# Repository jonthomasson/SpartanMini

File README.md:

# SpartanMini
A flexible, simple, yet powerful FPGA development board.

As is the case with many things, the Spartan Mini was born out of a need I had when developing an FPGA project. I looked around at the development boards in the market, but I didn't see anything that met all of my requirements, so I decided to design one myself. There were many requirements for this board, which I will go into more detail about in the details section below, but my general requirements were as follows. I wanted a board I could hand solder fairly easily. This meant no bga. I wanted a board that was easy to program, containing both a JTAG port as well as USB. I wanted a board I could power with a wall wart and a barrel jack. The power needed to be switched. There needed to be plenty of GPIO, brought out to connectors that were preferably of a standardized format. I wanted some onboard RAM, preferrably SRAM or PSRAM for ease of use. Other than that I just wanted access to the bare metal of the FPGA, without a lot of fluff.

Continuing from the requirements stated in the description, here is a more in depth look at those requirements and how the Spartan Mini meets them:

1. A board that could be hand soldered fairly easily.

It seems like 90% or more of the FPGA's out there are in a BGA package. This made things difficult when considering this spec. I finally settled on the Spartan 6 FPGA because it came in a 144 pin TQFP package. The Spartan 6 is a well known and well supported FPGA among hackers and makers, making it a perfect candidate for the job.

2. A board that could be programmed easily with either JTAG or USB.

For the USB portion of this requirement, I decide to use the FT2232H chip by FTDI. This chip gave me both a USB to JTAG channel, as well as a USB to UART bridge that I could use later on to facilitate transferring data to the FPGA over the USB connection. I also wanted to include a full size 14 pin JTAG connector on board, to facilitate the use of a Xilinx Platform Cable USB programmer. This took a little more board space, but provides an easier interface to connect to the Xilinx programmer.

3. A board that could be powered with a wall wart and barrel jack.

This requirement was fairly simple to implement. The voltage requirements for the board fall between 3.7-6 volts dc. In addition to the barrel jack, the board provides jumpers to optionally be powered over USB, or a JST-PH connector and 3.7 volt lithium battery, as well as a voltage input pin.

4. The power needed to have a hard on/off switch.

Again, this requirement was not hard to implement. I just needed to select an adequate switch, capable of handling the current demands of the board.

5. No IO pin of the FPGA should be wasted. All pins should be brought out to standardized connectors on the edges of the board.

Many FPGA boards today seem like they waste a lot of IO on providing connectors on board that likely aren't needed by every project such as SD cards, VGA, HDMI, etc. Instead of using up the IO on peripherals that may be unneeded I opted to instead route all GPIO lines out to PMOD connectors. These connectors seem to be picking up in popularity and there are already tons of sensors/peripherals to choose from in the marketplace that can be plugged into the board if/when they're needed. In addition to the GPIO, I also wired GPIO pins to 8 user programmable LED's, 2 tactile buttons, and 1 slide switch. The addition of the 8 LED's aids greatly in debugging, but it also allows for precisely one byte of data to be represented in binary.

6. Access to onboard SRAM or PSRAM

This requirement is simply for the ease of use of SRAM over DRAM. The downside to SRAM is of course the price, which is why I settled on PSRAM instead. Essentially PSRAM provides an interface to the outside world that looks like SRAM, while internally it is made up of DRAM. As such, it is much cheaper than SRAM, but way less work to interface with than DRAM. This particular board provides 8Mb of PSRAM, which is adequate for my needs.

![enter image description here](https://lh3.googleusercontent.com/Ym8JBT1FlSJsortWRAH4dx5KHW2HkV1B4FOYHD6TUoF2Va7fMqjjbZRKk-YTAfOauaZ6iTyjpKmPpW8K9U_Lzy1sPvceVg2OTIK4zidJ0OYhVarUZ6AJo-_n0Bh1tX8kFqed3uyobCEtJzAthKT_NUfyR5vuuTG_k4TjL7J-cD8Y5W50PloVUXzOydISsuWan971t84IHQZvExRTL13VKr9Dzf7VFZQ4-1O7Eb2D59EVHCMWfp65vcO2BCi3f3q-bV_YtxEnLM_6e8DsP4a7GdczFiddMFkXQBkkdZaEMM2iFYc0Uvn_fpE_hW8l_2niM3Bjweu2Sg1JI46zMwf1BJlQvk6hKFwMn6nt-VLBW11oDaMBjqX9CXKMFm71dwxRTxzdKROl2nzPsxBll-ldlJ9pS-G4F2r8SEyl_1cLp4FI9L6Toqehjpdptvo6k-bQtzZX9d7uxOGFWja2dMNWYFRKiI2IBQzqyreGzzcMScAPFWFUQucwtIUtVOjU9eformU7DzSAqNybfNj_1Cf66kgaPlsM0UQ6a2LvAtUDOFYDCX_l58AIW41YAItvtlo8zSZ7KETyjbF2bbkrhY29mfstlfJ0lxFEip1irmiC=w1223-h688-no)

Here's a pic of the finished proto shield:
![enter image description here](https://lh3.googleusercontent.com/XVl9vBILrFzYoo-aqGuPinKMaAg1SiMGnw2o0brUdcbjzrX_OM7FDiEOOaxkABmsGx_YnNGTo_vhjEov2aorHuK09fe5Of0MSD2nyAMjhmHx2-vPp61wXmYYEb9uJpriS7c-KQS3IXlFl3N068_lc_-l7lU_sf3SuPzvnHECnoO0J4L6pnPQVym1PMrDh47Fw-OdFCAAsPRn38aGkLim3vHlUNbdCeJ7o2DY7dQxQNxw3rlYhkYHu8ck_lHzUk-93gGGT9lEoZzGOoJ5PW-e5-kHvbxesEgOWf7VaKeEmJR0SyLdO2nTZNo8BzTyuRD0KrKwcO2678YBeTiLqef4WfJXKnJdRhSgQjhQ-s72llQxLT6zsE_KIJDUy6Yd8EM9Fzlg9KmEdMNf-uqJ4Ht_2Hn0ylL2g0QgoXBpAplv5dJR7Py4TpnUCzPOWrd63cMVwbfEfk8FLc2Xi8dEvnVO9D8D-NkFfG4Thc_I4GchgRej_VKDMysdUIFXAmFLjOvsaycX8eAK-RTY47NzNEG65PhANNQOsBYcIzGDWJXmgfrrhz2uPa8Q47qfnD9Brrmjvd-rsr0FU_VZmEmJzgSOTgQjifBuex9lx5Dea8zO=w1688-h949-no)

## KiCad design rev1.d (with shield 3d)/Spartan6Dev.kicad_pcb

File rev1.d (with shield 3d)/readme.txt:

--Main change from 1.c: I added right angle switches to provide access for eventual daughter boards. I also put sw2 on the board edge to provide additional access if a daughter board was connected. Also added a VIN/GND pin for external power to be fed in via daughter board, etc.

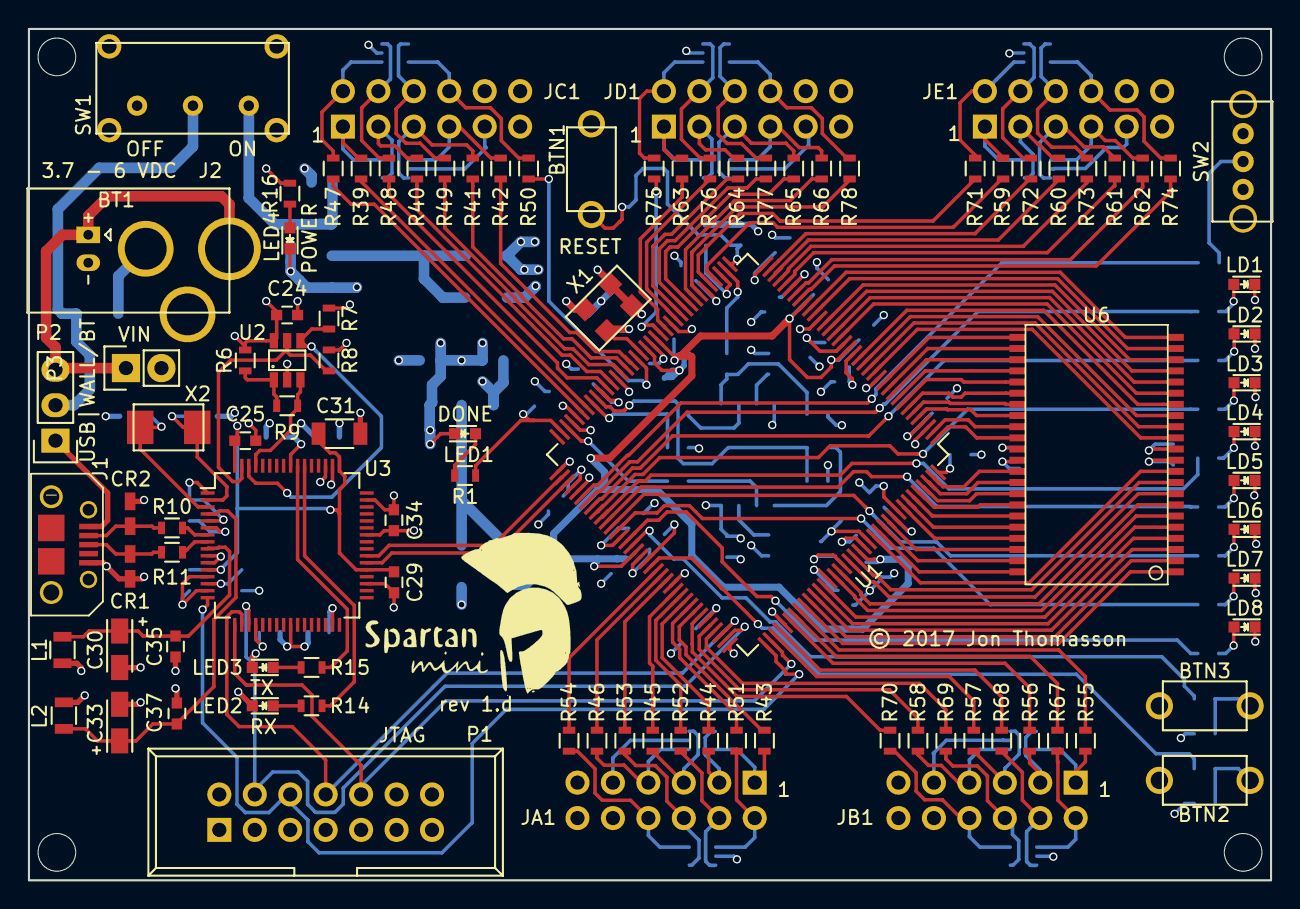
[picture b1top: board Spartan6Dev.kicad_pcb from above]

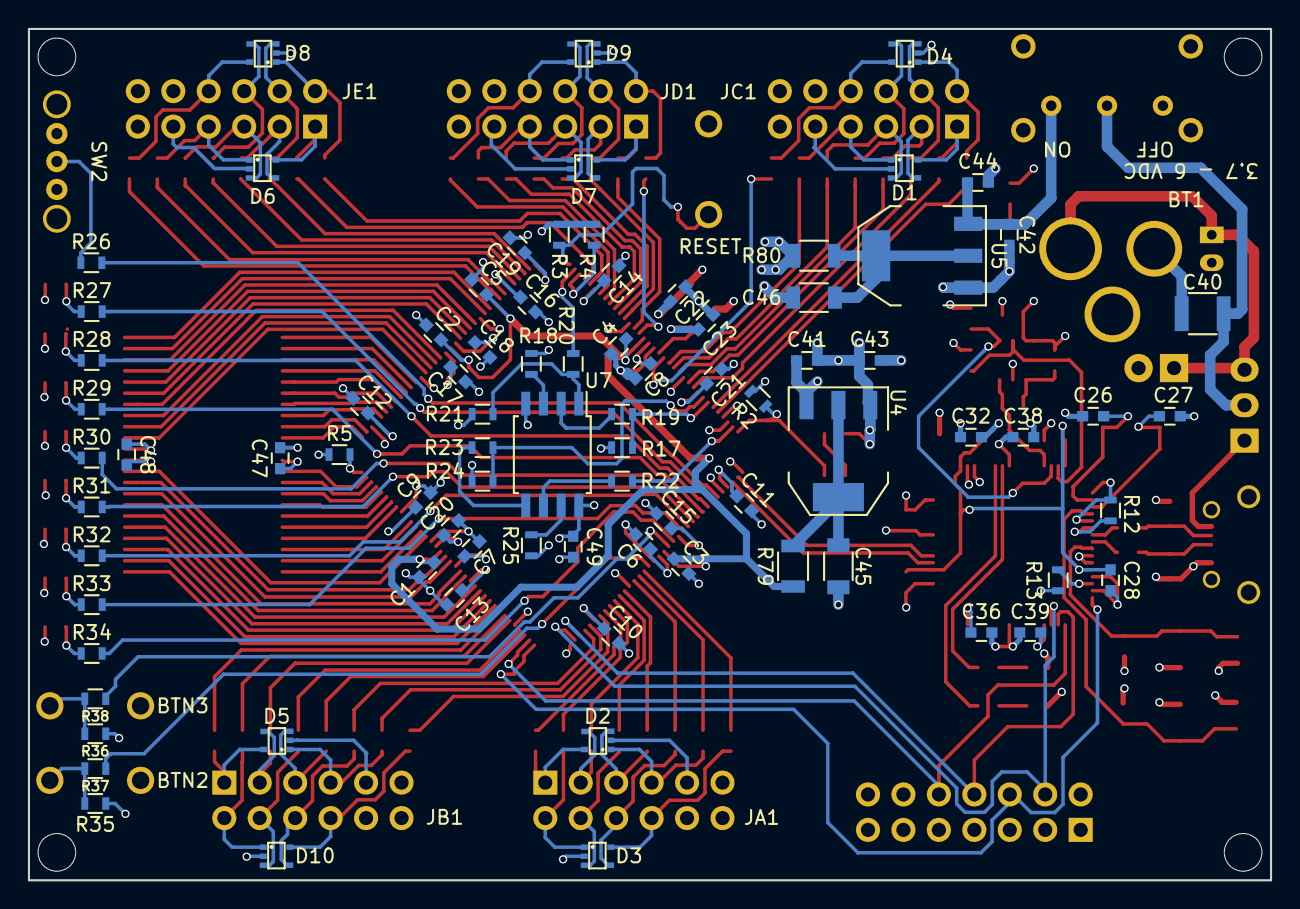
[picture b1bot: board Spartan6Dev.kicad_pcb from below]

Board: 4 copper layers, 89.0 x 61.0 mm, 180 parts (83 on the bottom side), 193 nets.

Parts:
BT1: JST-PH 3.7V BAT; JST_PH_S2B-PH-K_02x2.00mm
BTN1: BTN_RESET; SWITCH_1825966_1
BTN2, BTN3: BTN_PUSH; SWITCH_1825966_1
C1, C2, C3, C4, C5, C6, C7, C8, C9, C10, C11, C12, C13, C14, C15, C16, C17, C18, C19, C20, C21, C24, C25, C28, C29, C32, C34, C35, C36, C37, C38, C39, C41, C42, C47, C48, C49: .1uF; C_0603
C22: .01uF; C_0603
C23, C26, C27: 18pF; C_0603
C30, C33: 4.7uF; TantalC_SizeA_EIA-3216_Reflow
C31: 3.3uF; C_1206
C40: 47uF; C_1210
C43, C44: 1uF; C_0603
C45, C46: 10uF; C_1206
CR1, CR2: D_TVS; D_TVS_PGB1010603
D1, D2, D3, D4, D5, D6, D7, D8, D9, D10: NSQA6V8AW5T2; SOT323_5_NSQA6V8AW5T2
J1: USB MICRO; MICRO_USB_10118194
J2: BARREL_JACK; Barrel_Jack_PJ002A
JA1: PMA; Socket_Strip_Angled_2x06_PMOD
JB1: PMB; Socket_Strip_Angled_2x06_PMOD
JC1: PMC; Socket_Strip_Angled_2x06_PMOD
JD1: PMD; Socket_Strip_Angled_2x06_PMOD
JE1: PME; Socket_Strip_Angled_2x06_PMOD
L1, L2: L_Small; R_0805
LD1, LD2, LD3, LD4, LD5, LD6, LD7, LD8: LED; LED_0603
LED1: DONE_LED; LED_0603
LED2: RX_LED; LED_0603
LED3: TX_LED; LED_0603
LED4: PWR_LED; LED_0603
P1: JTAG; IDC_Header_Straight_14pins
P2: PWR_SELECT; Pin_Header_Straight_1x03
P3: VIN; Pin_Header_Straight_1x02
R1, R2, R14, R15: 220; R_0603
R3, R4, R5: 4.7K; R_0603
R6, R7, R8, R17, R20, R21, R24, R25, R26, R35, R36, R37, R38: 10K; R_0603
R9: 2K; R_0603
R10, R11: 10; R_0603
R12: 12K; R_0603
R13: 1K; R_0603
R16: 470; R_0603
R18, R19, R22, R23, R43, R44, R45, R46, R51, R52, R53, R54, R55, R56, R57, R58, R67, R68, R69, R70: 0; R_0603
R27, R28, R29, R30, R31, R32, R33, R34: 330; R_0603
R39, R40, R41, R42, R47, R48, R49, R50, R59, R60, R61, R62, R63, R64, R65, R66, R71, R72, R73, R74, R75, R76, R77, R78: 200; R_0603
R79, R80: 0; R_1206
SW1: SWITCH_PWR; SWITCH_SPDT_EG1224
SW2: SWITCH_INV; SWITCH_SPDT_OS102011MA1QN1
U1: XC6SLX9-2TQG144C; TQFP-144_20x20mm_Pitch0.5mm
U2: 93LC46B; SOT-23-6
U3: FT2232H; LQFP-64_10x10mm_Pitch0.5mm
U4: TLV1117LV12; SOT-223
U5: TLV1117LV33; SOT-223
U6: IS66WV51216EBL; tsop2-44
U7: M25P16; SOIJ-8_5.3x5.3mm_Pitch1.27mm
X1: FXO-HC536R; OSCILLATOR_FXO_HC53
X2: 12MHz; CRYSTAL_ABM3

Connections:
/fpga/A0: U1.121, U6.5
/fpga/A1: U1.120, U6.4
/fpga/A2: U1.119, U6.3
/fpga/A3: U1.118, U6.2
/fpga/A4: U1.117, U6.1
/fpga/A5: U1.132, U6.44
/fpga/A6: U1.133, U6.43
/fpga/A7: U1.134, U6.42
/fpga/A8: U1.8, U6.27
/fpga/A9: U1.9, U6.26
/fpga/A10: U1.10, U6.25
/fpga/A11: U1.11, U6.24
/fpga/A12: U1.27, U6.22
/fpga/A13: U1.26, U6.21
/fpga/A14: U1.24, U6.20
/fpga/A15: U1.23, U6.19
/fpga/A16: U1.22, U6.18
/fpga/A17: U1.12, U6.23
/fpga/A18: U1.7, U6.28
/fpga/BTN0: R37.1, U1.92
/fpga/BTN1: R38.1, U1.88
/fpga/CS: U1.123, U6.6
/fpga/D0: U1.124, U6.7
/fpga/D1: U1.126, U6.8
/fpga/D2: U1.127, U6.9
/fpga/D3: U1.131, U6.10
/fpga/D4: U1.14, U6.13
/fpga/D5: U1.15, U6.14
/fpga/D6: U1.16, U6.15
/fpga/D7: U1.17, U6.16
/fpga/D8: U1.6, U6.29
/fpga/D9: U1.5, U6.30
/fpga/D10: U1.2, U6.31
/fpga/D11: U1.1, U6.32
/fpga/D12: U1.143, U6.35
/fpga/D13: U1.142, U6.36
/fpga/D14: U1.141, U6.37
/fpga/D15: U1.140, U6.38
/fpga/DONE: R1.2, R2.1, U1.71
/fpga/GCLK: C23.1, U1.55, X1.3
/fpga/HSWAP: R5.2, U1.144
/fpga/INIT_B: R4.2, U1.39
/fpga/LB: U1.139, U6.39
/fpga/LED0: R27.2, U1.79
/fpga/LED1: R28.2, U1.80
/fpga/LED2: R29.2, U1.81
/fpga/LED3: R30.2, U1.82
/fpga/LED4: R31.2, U1.83
/fpga/LED5: R32.2, U1.84
/fpga/LED6: R33.2, U1.85
/fpga/LED7: R34.2, U1.87
/fpga/OE: U1.137, U6.41
/fpga/PMA0: R43.2, U1.101
/fpga/PMA1: R44.2, U1.99
/fpga/PMA2: R45.2, U1.97
/fpga/PMA3: R46.2, U1.94
/fpga/PMA4: R51.2, U1.100
/fpga/PMA5: R52.2, U1.98
/fpga/PMA6: R53.2, U1.95
/fpga/PMA7: R54.2, U1.93
/fpga/PMB0: R55.2, U1.116
/fpga/PMB1: R56.2, U1.114
/fpga/PMB2: R57.2, U1.111
/fpga/PMB3: R58.2, U1.104
/fpga/PMB4: R67.2, U1.115
/fpga/PMB5: R68.2, U1.112
/fpga/PMB6: R69.2, U1.105
/fpga/PMB7: R70.2, U1.102
/fpga/PMC0: R39.2, U1.66
/fpga/PMC1: R40.2, U1.61
/fpga/PMC2: R41.2, U1.58
/fpga/PMC3: R42.2, U1.57
/fpga/PMC4: R47.2, U1.67
/fpga/PMC5: R48.2, U1.62
/fpga/PMC6: R49.2, U1.59
/fpga/PMC7: R50.2, U1.56
/fpga/PMD0: R63.2, U1.50
/fpga/PMD1: R64.2, U1.47
/fpga/PMD2: R65.2, U1.45
/fpga/PMD3: R66.2, U1.44
/fpga/PMD4: R75.2, U1.51
/fpga/PMD5: R76.2, U1.48
/fpga/PMD6: R77.2, U1.46
/fpga/PMD7: R78.2, U1.43
/fpga/PME0: R59.2, U1.40
/fpga/PME1: R60.2, U1.34
/fpga/PME2: R61.2, U1.32
/fpga/PME3: R62.2, U1.30
/fpga/PME4: R71.2, U1.41
/fpga/PME5: R72.2, U1.35
/fpga/PME6: R73.2, U1.33
/fpga/PME7: R74.2, U1.29
/fpga/PROGB: BTN1.2, R3.2, U1.37
/fpga/RXD: U1.74, U3.39
/fpga/SCK: R22.1, U1.70
/fpga/SCS: R18.2, U1.38
/fpga/SDI: R17.1, R19.2, U1.65
/fpga/SDO: R23.1, R24.1, U1.64
/fpga/SW0: R26.2, U1.78
/fpga/TCK: P1.6, U1.109, U3.16
/fpga/TDI: P1.10, U1.110, U3.17
/fpga/TDO: P1.8, U1.106, U3.18
/fpga/TMS: P1.4, U1.107, U3.19
/fpga/TXD: U1.75, U3.38
/fpga/UB: U1.138, U6.40
/fpga/VCC3V3: BTN2.1, BTN3.1, C6.1, C7.1, C8.1, C9.1, C10.1, C11.1, C12.1, C13.1, C14.1, C15.1, C16.1, C17.1, C18.1, C19.1, C20.1, C21.1, C22.1, C24.1, C32.2, C34.1, C36.1, C38.1, C39.1, C41.1, C43.1, C47.1, C48.1, C49.2, JA1.6, JA1.12, JB1.6, JB1.12, JC1.6, JC1.12, JD1.6, JD1.12, JE1.6, JE1.12, L1.1, L2.1, LED2.2, LED3.2, P1.2, R2.2, R3.1, R4.1, R5.1, R6.1, R7.1, R8.1, R13.2, R16.1, R17.2, R20.1, R21.1, R24.2, R25.1, R80.1, SW2.1, U1.4, U1.18, U1.20, U1.31, U1.36, U1.42, U1.53, U1.63, U1.69, U1.76, U1.86, U1.90, U1.103, U1.122, U1.125, U1.129, U1.135, U2.6, U3.20, U3.31, U3.42, U3.50, U3.56, U4.3, U6.11, U6.33, U7.8, X1.1, X1.4
/fpga/VCCINT: C1.1, C2.1, C3.1, C4.1, C5.1, R79.1, U1.19, U1.28, U1.52, U1.89, U1.128
/fpga/WE: U1.21, U6.17
/power/VCCIN: C40.1, P2.2, SW1.2
/power/VUSB: J1.1, P2.1
/usb/VCORE: C25.1, C28.1, C29.1, C31.1, U3.12, U3.37, U3.49, U3.64
GND: BT1.2, BTN1.1, C1.2, C2.2, C3.2, C4.2, C5.2, C6.2, C7.2, C8.2, C9.2, C10.2, C11.2, C12.2, C13.2, C14.2, C15.2, C16.2, C17.2, C18.2, C19.2, C20.2, C21.2, C22.2, C23.2, C24.2, C25.2, C26.1, C27.1, C28.2, C29.2, C30.2, C31.2, C32.1, C33.2, C34.2, C35.2, C36.2, C37.2, C38.2, C39.2, C40.2, C41.2, C42.2, C43.2, C44.2, C45.2, C46.2, C47.2, C48.2, C49.1, CR1.2, CR2.2, D1.2, D2.2, D3.2, D4.2, D5.2, D6.2, D7.2, D8.2, D9.2, D10.2, J1.5, J2.2, JA1.5, JA1.11, JB1.5, JB1.11, JC1.5, JC1.11, JD1.5, JD1.11, JE1.5, JE1.11, LD1.1, LD2.1, LD3.1, LD4.1, LD5.1, LD6.1, LD7.1, LD8.1, LED1.1, LED4.1, P1.1, P1.3, P1.5, P1.7, P1.9, P1.11, P1.13, P3.2, R12.2, R35.1, R36.1, SW2.3, U1.3, U1.13, U1.25, U1.49, U1.54, U1.60, U1.68, U1.73, U1.77, U1.91, U1.96, U1.108, U1.113, U1.130, U1.136, U2.2, U3.1, U3.5, U3.10, U3.11, U3.13, U3.15, U3.25, U3.35, U3.47, U3.51, U4.1, U5.1, U6.12, U6.34, U7.4, X1.2
unnamed: BT1.1, J2.1, P2.3, P3.1
unnamed: BTN2.2, R35.2, R37.2
unnamed: BTN3.2, R36.2, R38.2
unnamed: C26.2, U3.2, X2.1
unnamed: C27.2, U3.3, X2.2
unnamed: C30.1, C35.1, L1.2, U3.9
unnamed: C33.1, C37.1, L2.2, U3.4
unnamed: C42.1, C44.1, SW1.3, U5.3
unnamed: C45.1, R79.2, U4.2, U4.4
unnamed: C46.1, R80.2, U5.2, U5.4
unnamed: CR1.1, J1.3, R11.2
unnamed: CR2.1, J1.2, R10.2
unnamed: D1.1, JC1.4, R42.1
unnamed: D1.3, JC1.3, R41.1
unnamed: D1.4, JC1.2, R40.1
unnamed: D1.5, JC1.1, R39.1
unnamed: D2.1, JA1.4, R46.1
unnamed: D2.3, JA1.3, R45.1
unnamed: D2.4, JA1.2, R44.1
unnamed: D2.5, JA1.1, R43.1
unnamed: D3.1, JA1.7, R51.1
unnamed: D3.3, JA1.8, R52.1
unnamed: D3.4, JA1.9, R53.1
unnamed: D3.5, JA1.10, R54.1
unnamed: D4.1, JC1.7, R47.1
unnamed: D4.3, JC1.8, R48.1
unnamed: D4.4, JC1.9, R49.1
unnamed: D4.5, JC1.10, R50.1
unnamed: D5.1, JB1.4, R58.1
unnamed: D5.3, JB1.3, R57.1
unnamed: D5.4, JB1.2, R56.1
unnamed: D5.5, JB1.1, R55.1
unnamed: D6.1, JE1.4, R62.1
unnamed: D6.3, JE1.3, R61.1
unnamed: D6.4, JE1.2, R60.1
unnamed: D6.5, JE1.1, R59.1
unnamed: D7.1, JD1.4, R66.1
unnamed: D7.3, JD1.3, R65.1
unnamed: D7.4, JD1.2, R64.1
unnamed: D7.5, JD1.1, R63.1
unnamed: D8.1, JE1.7, R71.1
unnamed: D8.3, JE1.8, R72.1
unnamed: D8.4, JE1.9, R73.1
unnamed: D8.5, JE1.10, R74.1
unnamed: D9.1, JD1.7, R75.1
unnamed: D9.3, JD1.8, R76.1
unnamed: D9.4, JD1.9, R77.1
unnamed: D9.5, JD1.10, R78.1
unnamed: D10.1, JB1.7, R67.1
unnamed: D10.3, JB1.8, R68.1
unnamed: D10.4, JB1.9, R69.1
unnamed: D10.5, JB1.10, R70.1
unnamed: LD1.2, R27.1
unnamed: LD2.2, R28.1
unnamed: LD3.2, R29.1
unnamed: LD4.2, R30.1
unnamed: LD5.2, R31.1
unnamed: LD6.2, R32.1
unnamed: LD7.2, R33.1
unnamed: LD8.2, R34.1
unnamed: LED1.2, R1.1
unnamed: LED2.1, R14.1
unnamed: LED3.1, R15.1
unnamed: LED4.2, R16.2
unnamed: R6.2, R9.2, U2.1
unnamed: R7.2, U2.4, U3.62
unnamed: R8.2, U2.5, U3.63
unnamed: R9.1, U2.3, U3.61
unnamed: R10.1, U3.7
unnamed: R11.1, U3.8
unnamed: R12.1, U3.6
unnamed: R13.1, U3.14
unnamed: R14.2, U3.54
unnamed: R15.2, U3.55
unnamed: R18.1, R21.2, U7.1
unnamed: R19.1, U7.2
unnamed: R20.2, U7.3
unnamed: R22.2, U7.6
unnamed: R23.2, U7.5
unnamed: R25.2, U7.7
unnamed: R26.1, SW2.2

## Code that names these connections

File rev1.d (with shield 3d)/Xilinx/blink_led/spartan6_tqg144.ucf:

## This file is a general .ucf for the Spartan Mini rev 1.d board
## To use it in a project:
## - remove or comment the lines corresponding to unused pins
## - rename the used signals according to the project

##========================================================
## Clock signal
##========================================================
NET "clk" TNM_NET = clk;
TIMESPEC TS_clk = PERIOD "clk" 100 MHz HIGH 50%;

NET "clk"    LOC = P55;

##=========================================================
## 1 slide switch
##==========================================================			
#NET "sw1"  LOC = P78;

##========================================================
## Buttons
##========================================================
#NET "btn_n<0>"   LOC = P92;	
#NET "btn_n<1>"   LOC = P88;
#NET "reset_n"  	LOC = P37;	

##========================================================
## Usb-RS232 interface
##========================================================
#NET "Rx"  LOC = P74	| IOSTANDARD = "LVCMOS33"; 	
#NET "Tx"  LOC = P75	| IOSTANDARD = "LVCMOS33"; 	

##========================================================
## programmable leds
##========================================================
NET "led<0>"  LOC = P79	| IOSTANDARD = "LVCMOS33"; 	
NET "led<1>"  LOC = P80	| IOSTANDARD = "LVCMOS33"; 	
NET "led<2>"  LOC = P81	| IOSTANDARD = "LVCMOS33"; 
NET "led<3>"  LOC = P82	| IOSTANDARD = "LVCMOS33"; 	
NET "led<4>"  LOC = P83	| IOSTANDARD = "LVCMOS33"; 
NET "led<5>"  LOC = P84	| IOSTANDARD = "LVCMOS33"; 
NET "led<6>"  LOC = P85	| IOSTANDARD = "LVCMOS33"; 
NET "led<7>"  LOC = P87	| IOSTANDARD = "LVCMOS33"; 

##========================================================
## PSRAM 8Mb
##========================================================
#NET "MemAdr<0>"  LOC = P121	| IOSTANDARD = "LVCMOS33"; 	
#NET "MemAdr<1>"  LOC = P120	| IOSTANDARD = "LVCMOS33"; 	
#NET "MemAdr<2>"  LOC = P119	| IOSTANDARD = "LVCMOS33"; 	
#NET "MemAdr<3>"  LOC = P118	| IOSTANDARD = "LVCMOS33"; 	
#NET "MemAdr<4>"  LOC = P117	| IOSTANDARD = "LVCMOS33"; 	
#NET "MemAdr<5>"  LOC = P132	| IOSTANDARD = "LVCMOS33"; 	
#NET "MemAdr<6>"  LOC = P133	| IOSTANDARD = "LVCMOS33"; 	
#NET "MemAdr<7>"  LOC = P134	| IOSTANDARD = "LVCMOS33"; 	
#NET "MemAdr<8>"  LOC = P8	| IOSTANDARD = "LVCMOS33"; 	
#NET "MemAdr<9>"  LOC = P9	| IOSTANDARD = "LVCMOS33"; 	
#NET "MemAdr<10>"  LOC = P10	| IOSTANDARD = "LVCMOS33"; 	
#NET "MemAdr<11>"  LOC = P11	| IOSTANDARD = "LVCMOS33"; 	
#NET "MemAdr<12>"  LOC = P27	| IOSTANDARD = "LVCMOS33"; 	
#NET "MemAdr<13>"  LOC = P26	| IOSTANDARD = "LVCMOS33"; 	
#NET "MemAdr<14>"  LOC = P24	| IOSTANDARD = "LVCMOS33"; 	
#NET "MemAdr<15>"  LOC = P23	| IOSTANDARD = "LVCMOS33"; 	
#NET "MemAdr<16>"  LOC = P22	| IOSTANDARD = "LVCMOS33"; 	
#NET "MemAdr<17>"  LOC = P12	| IOSTANDARD = "LVCMOS33"; 	
#NET "MemAdr<18>"  LOC = P7	| IOSTANDARD = "LVCMOS33"; 	

#NET "MemDB<0>"  LOC = P124	| IOSTANDARD = "LVCMOS33"; 	
#NET "MemDB<1>"  LOC = P126	| IOSTANDARD = "LVCMOS33"; 	
#NET "MemDB<2>"  LOC = P127	| IOSTANDARD = "LVCMOS33"; 	
#NET "MemDB<3>"  LOC = P131	| IOSTANDARD = "LVCMOS33"; 	
#NET "MemDB<4>"  LOC = P14	| IOSTANDARD = "LVCMOS33"; 	
#NET "MemDB<5>"  LOC = P15	| IOSTANDARD = "LVCMOS33"; 	
#NET "MemDB<6>"  LOC = P16	| IOSTANDARD = "LVCMOS33"; 	
#NET "MemDB<7>"  LOC = P17	| IOSTANDARD = "LVCMOS33"; 	
#NET "MemDB<8>"  LOC = P6	| IOSTANDARD = "LVCMOS33"; 	
#NET "MemDB<9>"  LOC = P5	| IOSTANDARD = "LVCMOS33"; 	
#NET "MemDB<10>"  LOC = P2	| IOSTANDARD = "LVCMOS33"; 	
#NET "MemDB<11>"  LOC = P1	| IOSTANDARD = "LVCMOS33"; 	
#NET "MemDB<12>"  LOC = P143	| IOSTANDARD = "LVCMOS33"; 	
#NET "MemDB<13>"  LOC = P142	| IOSTANDARD = "LVCMOS33"; 	
#NET "MemDB<14>"  LOC = P141	| IOSTANDARD = "LVCMOS33"; 	
#NET "MemDB<15>"  LOC = P140	| IOSTANDARD = "LVCMOS33"; 	

#NET "RamUB"  LOC = P138	| IOSTANDARD = "LVCMOS33"; 	
#NET "RamLB"  LOC = P139	| IOSTANDARD = "LVCMOS33"; 	
#NET "MemOE"  LOC = P137	| IOSTANDARD = "LVCMOS33"; 	
#NET "MemWR"  LOC = P21	| IOSTANDARD = "LVCMOS33"; 	
#NET "RamCS"  LOC = P123	| IOSTANDARD = "LVCMOS33"; 	

##========================================================
## 16Mb SPI Flash
##========================================================
#NET "SCS"  LOC = P38	| IOSTANDARD = "LVCMOS33"; 
#NET "SDI"  LOC = P65	| IOSTANDARD = "LVCMOS33"; 
#NET "SCK"  LOC = P70	| IOSTANDARD = "LVCMOS33"; 
#NET "SDO"  LOC = P64	| IOSTANDARD = "LVCMOS33"; 

##========================================================
## JA PMOD
##========================================================
#NET "JA<0>"  LOC = P101	| IOSTANDARD = "LVCMOS33"; 
#NET "JA<1>"  LOC = P99	| IOSTANDARD = "LVCMOS33"; 
#NET "JA<2>"  LOC = P97	| IOSTANDARD = "LVCMOS33"; 
#NET "JA<3>"  LOC = P94	| IOSTANDARD = "LVCMOS33"; 
#NET "ledtest"  LOC = P100	| IOSTANDARD = "LVCMOS33"; 
#NET "JA<5>"  LOC = P98	| IOSTANDARD = "LVCMOS33"; 
#NET "JA<6>"  LOC = P95	| IOSTANDARD = "LVCMOS33"; 
#NET "JA<7>"  LOC = P93	| IOSTANDARD = "LVCMOS33"; 

##========================================================
## JB PMOD
##========================================================
#NET "JB<0>"  LOC = P116	| IOSTANDARD = "LVCMOS33"; 
#NET "JB<1>"  LOC = P114	| IOSTANDARD = "LVCMOS33"; 
#NET "JB<2>"  LOC = P111	| IOSTANDARD = "LVCMOS33"; 
#NET "JB<3>"  LOC = P104	| IOSTANDARD = "LVCMOS33"; 
#NET "JB<4>"  LOC = P115	| IOSTANDARD = "LVCMOS33"; 
#NET "JB<5>"  LOC = P112	| IOSTANDARD = "LVCMOS33"; 
#NET "JB<6>"  LOC = P105	| IOSTANDARD = "LVCMOS33"; 
#NET "JB<7>"  LOC = P102	| IOSTANDARD = "LVCMOS33"; 

##========================================================
## JC PMOD
##========================================================
#NET "JC<0>"  LOC = P66	| IOSTANDARD = "LVCMOS33"; 
#NET "JC<1>"  LOC = P61	| IOSTANDARD = "LVCMOS33"; 
#NET "JC<2>"  LOC = P58	| IOSTANDARD = "LVCMOS33"; 
#NET "JC<3>"  LOC = P57	| IOSTANDARD = "LVCMOS33"; 
#NET "JC<4>"  LOC = P67	| IOSTANDARD = "LVCMOS33"; 
#NET "JC<5>"  LOC = P62	| IOSTANDARD = "LVCMOS33"; 
#NET "JC<6>"  LOC = P59	| IOSTANDARD = "LVCMOS33"; 
#NET "JC<7>"  LOC = P56	| IOSTANDARD = "LVCMOS33"; 

##========================================================
## JD PMOD
##========================================================
#NET "JD<0>"  LOC = P50	| IOSTANDARD = "LVCMOS33"; 
#NET "JD<1>"  LOC = P47	| IOSTANDARD = "LVCMOS33"; 
#NET "JD<2>"  LOC = P45	| IOSTANDARD = "LVCMOS33"; 
#NET "JD<3>"  LOC = P44	| IOSTANDARD = "LVCMOS33"; 
#NET "JD<4>"  LOC = P51	| IOSTANDARD = "LVCMOS33"; 
#NET "JD<5>"  LOC = P48	| IOSTANDARD = "LVCMOS33"; 
#NET "JD<6>"  LOC = P46	| IOSTANDARD = "LVCMOS33"; 
#NET "JD<7>"  LOC = P43	| IOSTANDARD = "LVCMOS33"; 

##========================================================
## JE PMOD
##========================================================
#NET "JE<0>"  LOC = P40	| IOSTANDARD = "LVCMOS33"; 
#NET "JE<1>"  LOC = P34	| IOSTANDARD = "LVCMOS33"; 
#NET "JE<2>"  LOC = P32	| IOSTANDARD = "LVCMOS33"; 
#NET "JE<3>"  LOC = P30	| IOSTANDARD = "LVCMOS33"; 
#NET "JE<4>"  LOC = P41	| IOSTANDARD = "LVCMOS33"; 
#NET "JE<5>"  LOC = P35	| IOSTANDARD = "LVCMOS33"; 
#NET "JE<6>"  LOC = P33	| IOSTANDARD = "LVCMOS33"; 
#NET "JE<7>"  LOC = P29	| IOSTANDARD = "LVCMOS33"; 

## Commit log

2017-04-20 :lollipop: Added .gitattributes & .gitignore files
2017-04-24 added template project for creating shields and new logo icon in logo folder.
2017-04-24 updated template project
2017-04-24 adding a second template project for power in addition to gpio.
2017-09-24 latest version with shield template and gerbers
2017-10-13 default config files for usb and ise
2017-11-11 added some sample xilinx projects
2017-11-15 some changes to propeller source for nes core
2017-11-17 finishing propeller serial upload program
2017-11-17 first working version using propeller for sd card/menu/game loading!

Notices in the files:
rev1.d (with shield 3d)/Spartan6Dev.kicad_pcb:
© 2017 Jon Thomasson
